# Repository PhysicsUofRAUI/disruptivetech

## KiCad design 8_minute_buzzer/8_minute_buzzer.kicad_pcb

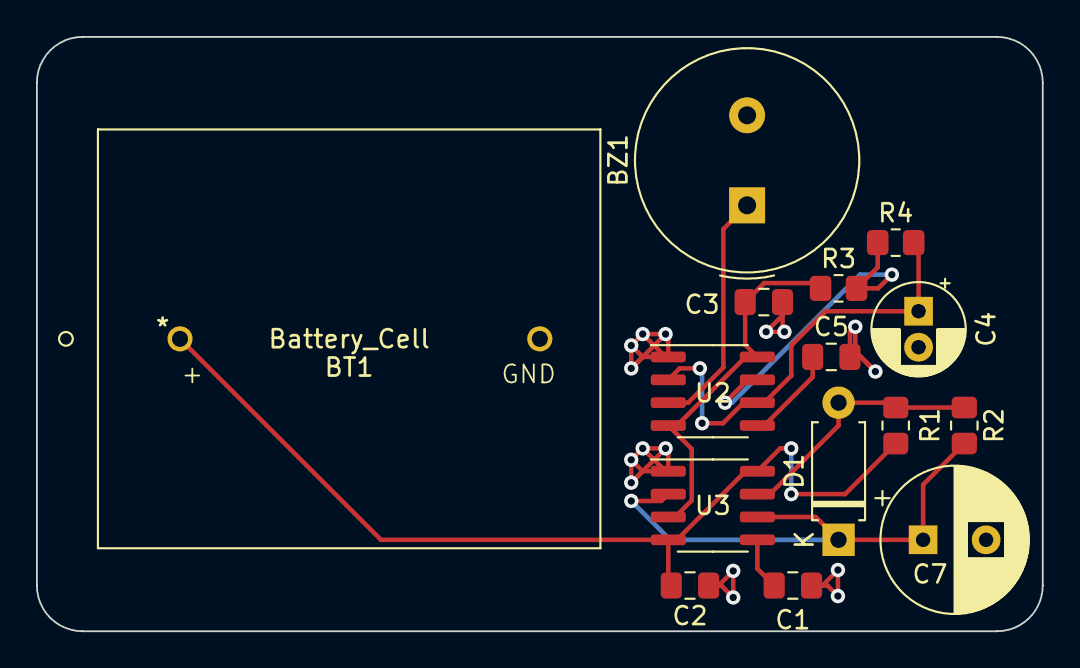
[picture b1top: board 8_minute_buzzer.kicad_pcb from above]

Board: 2 copper layers, 55.9 x 33.0 mm, 15 parts (0 on the bottom side), 10 nets.

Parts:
BT1: Battery_Cell; 1066
BZ1: Buzzer; Buzzer_TDK_PS1240P02BT_D12.2mm_H6.5mm
C1, C3, C5: 0.01u; C_0805_2012Metric_Pad1.18x1.45mm_HandSolder
C2: 0.01; C_0805_2012Metric_Pad1.18x1.45mm_HandSolder
C4: 0.1uF; CP_Radial_D5.0mm_P2.00mm
C7: 3.3u; CP_Radial_D8.0mm_P3.50mm
D1: D; D_A-405_P7.62mm_Horizontal
R1: 437k; R_0805_2012Metric_Pad1.20x1.40mm_HandSolder
R2: 209M; R_0805_2012Metric_Pad1.20x1.40mm_HandSolder
R3: 220; R_0805_2012Metric_Pad1.20x1.40mm_HandSolder
R4: 10k; R_0805_2012Metric_Pad1.20x1.40mm_HandSolder
U2, U3: TLC555xD; SOIC-8_3.9x4.9mm_P1.27mm

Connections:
/timer_out: C3.1, R3.1, U2.4 (R), U2.8 (VCC), U3.3 (Q)
GND: BT1.2 (-), BZ1.2 (+), C1.2, C2.1, C3.2, C4.2, C5.2, C7.2, U2.1 (GND), U3.1 (GND)
unnamed: BZ1.1 (-), U2.3 (Q)
unnamed: D1.2 (A), R1.2, R2.1, U3.7 (DIS)
unnamed: C7.1, D1.1 (K), R2.2, U3.2 (TR), U3.6 (THR)
unnamed: C5.1, U2.5 (CV)
unnamed: R3.2, R4.1, U2.7 (DIS)
unnamed: C4.1, R4.2, U2.2 (TR), U2.6 (THR)
unnamed: C1.1, U3.5 (CV)
VCC: BT1.1 (+), C2.2, R1.1, U3.4 (R), U3.8 (VCC)

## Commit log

2023-06-24 add first 8 minute buzzer version
2023-06-25 add pictures

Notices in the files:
parts and their libraries:
Copyright 2021 Accelerated Designs. All rights reserved.
